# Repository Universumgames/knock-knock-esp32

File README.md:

# Klap-Klap

- [Klap-Klap](#klap-klap)
  - [Description](#description)
  - [Important files and directories](#important-files-and-directories)
  - [Contributing Setup](#contributing-setup)
  - [Project setup](#project-setup)

URL to repository: https://github.com/Universumgames/knock-knock-esp32

## Description
This project is a simple knock pattern recognizer for a door or chest. The knock pattern is stored on an SD card connected to the ESP32. The knock pattern is recognized by the ESP32 and if the pattern is correct, the door or chest is unlocked. The lock is controlled by a solenoid lock. The project is written in C with the ESP-IDF and uses the PlatformIO IDE. The project is based on the ESP32-C3 microcontroller.

## Important files and directories
- [`documentation/sprint_plan.md`](documentation/sprint_plan.md): Contains the Sprint Plan and detailed description by whom the task was completed
- [`documentation/backlog.md`](documentation/backlog.md): Contains the backlog, a detailed beakdown of the seperate task of this project
- [`src/`](src/): Contains the source code of the project
- [`test/`](test/): Contains the test code of the project
- [`platformio.ini`](platformio.ini): Contains the configuration of the project
- [`README.md`](README.md): Contains the description of the project
- [`LICENSE`](LICENSE): Contains the license of the project
- [`CHANGELOG.md`](CHANGELOG.md): The changelog 
- [`lib/`](lib/): Contains the self written libraries
- [`documentation/`](documentation/): Contains the documentation of the project
- [`datasheets/`](datasheets/): Contains the datasheets for the used components
- [`docker/`](docker/): Contains the docker files to build the platformio environment in a docker container
- [`pinout.txt`](pinout.txt): Contains the pinout of the used microcontroller
- [`pcb/`](pcb/): Contains the pcb files

## Contributing Setup
- install clang-format
  - Debian/Ubuntu: `sudo apt install clang-format`
  - Arch: `sudo pacman -S clang`
  - MacOS: `brew install clang-format`
  - Windows: `pip3 install clang-format`
- configure githooks
  - run `git config core.hooksPath .githooks`
- configure IDE to use clang-format
  - VS Code: install the `Clang-Format` extension (https://marketplace.visualstudio.com/items?itemName=xaver.clang-format)
  - CLion: enable clang-format (https://www.jetbrains.com/help/clion/clangformat-as-alternative-formatter.html)

## Project setup

1. Install VS Code
2. Install PlatformIO extension
3. open PIO Home -> Platforms -> Espressif 32 -> Install (should be installed automatically when opening the project via PlatformIO)
4. building the project by clicking on checkmark in the bottom left corner (when hovering over it, it says: "Build")
5. run tests via the `pio test` command in the terminal

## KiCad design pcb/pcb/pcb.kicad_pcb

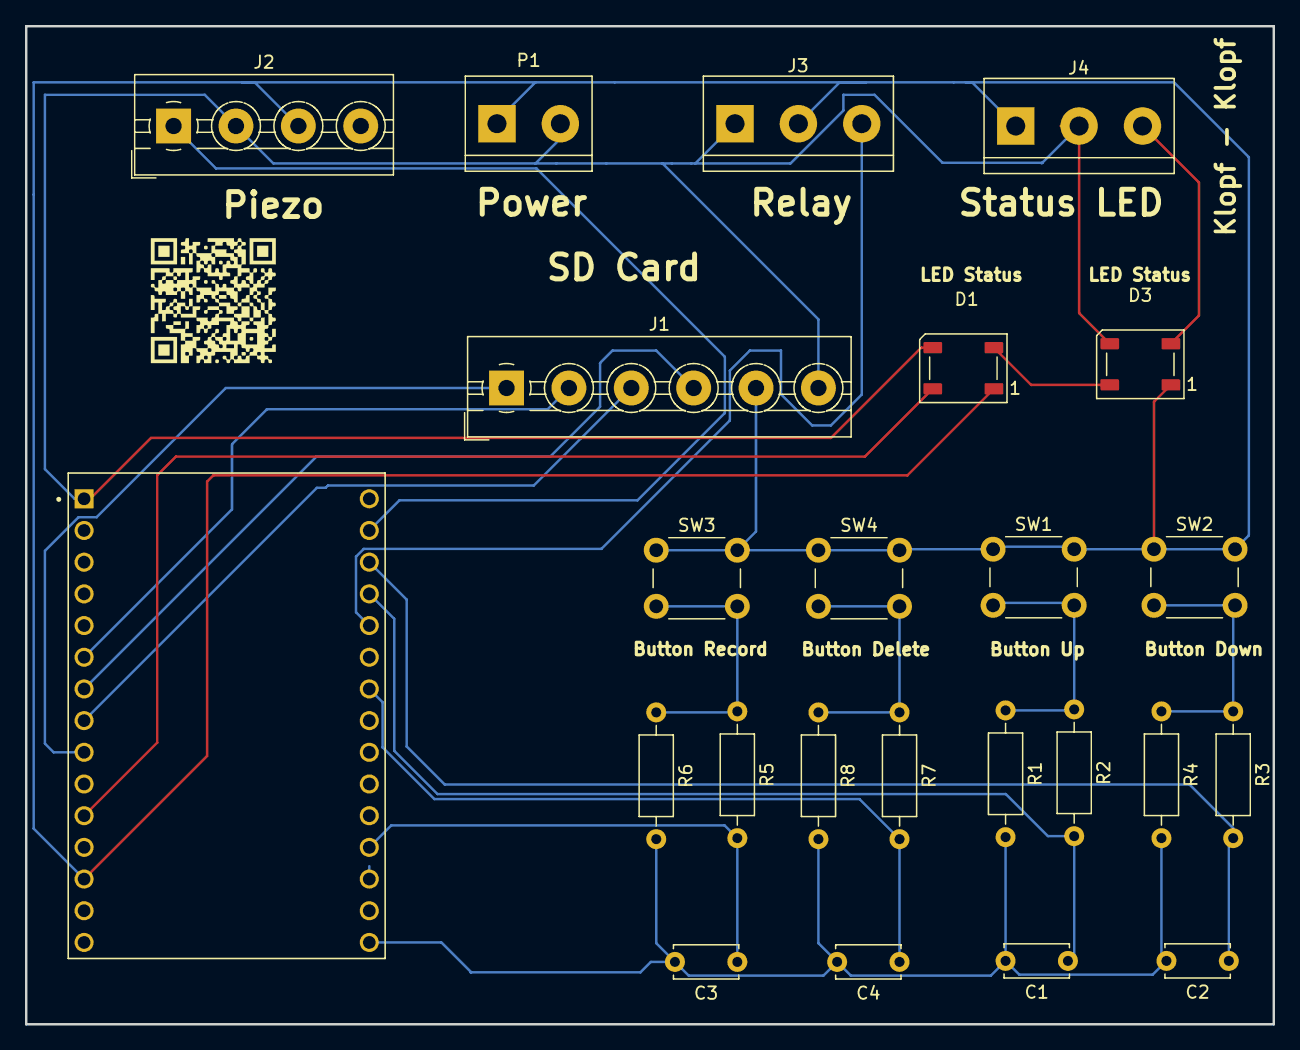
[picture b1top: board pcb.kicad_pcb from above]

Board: 2 copper layers, 100.0 x 80.0 mm, 24 parts (0 on the bottom side), 20 nets.

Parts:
C1, C2, C3, C4: 47nF; C_Disc_D5.0mm_W2.5mm_P5.00mm
D1, D3: WS2812B; LED_WS2812B_PLCC4_5.0x5.0mm_P3.2mm
J1: SD Card; TerminalBlock_MaiXu_MX126-5.0-06P_1x06_P5.00mm
J2: Mic; TerminalBlock_MaiXu_MX126-5.0-04P_1x04_P5.00mm
J3: Relay Solenoid; TerminalBlock_bornier-3_P5.08mm
J4: Status LED; TerminalBlock_bornier-3_P5.08mm
P1: Power; TerminalBlock_bornier-2_P5.08mm
R1, R4, R6, R8: 1kΩ; R_Axial_DIN0207_L6.3mm_D2.5mm_P10.16mm_Horizontal
R2, R3, R5, R7: 10kΩ; R_Axial_DIN0207_L6.3mm_D2.5mm_P10.16mm_Horizontal
SW1: Button Up; SW_PUSH_6mm_H4.3mm
SW2: Button Down; SW_PUSH_6mm_H4.3mm
SW3: Button Record; SW_PUSH_6mm_H4.3mm
SW4: Button Delete; SW_PUSH_6mm_H4.3mm
U1: ESP32-C3-DevKitC-02; XCVR_ESP32-C3-DEVKITC-02

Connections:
3V3: U1.2 (3V3), U1.3 (3V3)
5V: D1.1 (VDD), D3.1 (VDD), J1.5 (5V), J2.3 (5V), J3.2 (5V), J4.1 (5V), P1.1 (5V), SW1.1, SW2.1, SW3.1, SW4.1, U1.13 (5V), U1.14 (5V)
GND: C1.2, C2.2, C3.2, C4.2, D1.3 (VSS), D3.3 (VSS), J1.6 (GND), J2.2 (GND), J3.1 (GND), J4.2 (GND), P1.2 (GND), R1.2, R4.2, R6.2, R8.2, U1.1 (GND), U1.5 (GND), U1.10 (GND), U1.15 (GND), U1.16 (GND), U1.17 (GND), U1.20 (GND), U1.23 (GND), U1.25 (GND), U1.30 (GND)
unnamed: D1.4 (DIN), U1.11 (GPIO8/RGB_LED)
unnamed: D1.2 (DOUT), D3.4 (DIN)
unnamed: D3.2 (DOUT), J4.3 (Data)
unnamed: J1.1 (CS), U1.9 (GPIO7)
unnamed: J1.4 (MISO), U1.7 (GPIO5)
unnamed: J1.3 (MOSI), U1.8 (GPIO6)
unnamed: J1.2 (SCK), U1.6 (GPIO4)
unnamed: J2.1 (A0), U1.29 (GPIO0)
unnamed: J3.3 (S), U1.26 (GPIO3)
unnamed: R1.1, R2.1, SW1.2
unnamed: R3.1, R4.1, SW2.2
unnamed: R5.1, R6.1, SW3.2
unnamed: R7.1, R8.1, SW4.2
unnamed: C2.1, R3.2, U1.28 (GPIO1)
unnamed: C1.1, R2.2, U1.27 (GPIO2)
unnamed: C4.1, R7.2, U1.24 (GPIO10)
unnamed: C3.1, R5.2, U1.19 (GPIO18/USBD_-)

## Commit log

2024-10-04 init
2024-10-04 Add LICENSE
2024-10-04 switch to platformio
2024-10-05 first serial test
2024-10-06 update Serial, switch to cpp
2024-10-06 test assembler
2024-10-06 add cpp formatting config
2024-10-06 play around with hardware led
2024-10-07 bugfixes
2024-10-07 add datasheets
2024-10-07 update backlog
2024-10-08 fix led strip
2024-10-08 refactoring
2024-10-10 finish sprint plan
2024-10-10 test
2024-10-10 init storage
2024-10-10 cleanup main
2024-10-10 fertig heute
2024-10-10 cleanup
2024-10-11 update sprint plant
2024-10-11 add c++ defines
2024-10-11 add documentation to old functions
2024-10-11 implement storage driver first part
2024-10-11 add linked list
2024-10-11 update gitignore
2024-10-13 lock_open fertig
2024-10-13 fixed implementation in linked list
2024-10-13 add new pinout diagram, fix dependencies
2024-10-13 finish basic storage driver
2024-10-14 add pinout list
2024-10-14 finish (revision Tom, Jovan)
2024-10-14 remove all vs code files
2024-10-14 fix library includes
2024-10-14 add pcb
2024-10-14 update pcd mit Notöffnung
2024-10-16 update assets and schematic
2024-10-16 add first documentation file
2024-10-16 preparing documentation
2024-10-16 FInish documentation for Sprint 1 with Simon and Jovan
2024-10-17 update built type
2024-10-17 test ci/cd
2024-10-17 try fixing ci/cd
2024-10-17 try fix 2
2024-10-17 update-README-und-Text-Präsentation
2024-10-17 update Sprintplan
2024-10-17 try ci cd 3
2024-10-17 try cicd fix 4
2024-10-17 cicd try fix 5
2024-10-17 fix cicd try 7
2024-10-18 add testing framework and fix string methods
2024-10-18 fixed unit tests
2024-10-20 add basic definitions
2024-10-20 add fileExists and add comments for common file operations
2024-10-20 add error handling to mounting
2024-10-20 fix bug in lsDir
2024-10-20 add storage test
2024-10-20 add test templates
2024-10-20 fix main
2024-10-21 prepare analog read
2024-10-21 add changelog
2024-10-21 add additional expect for storage test
2024-10-21 preparing further implementation, adding analog read test task
2024-10-22 try fixing led
2024-10-22 implement basic analog read
2024-10-22 try fixing LED driver with spi control, not usable because overwriting storage bus
2024-10-22 add led spi explanation image
2024-10-23 trying out i2s (not working at all)
2024-10-24 trying out i2s lib (not working)
2024-10-24 simplifying rmt config
2024-10-24 simplify and remove old code
2024-10-24 updating basic def header
2024-10-24 update changelog generator
2024-10-24 update cpp header pragma
2024-10-24 add pattern storage
2024-10-25 init pattern storage
2024-10-25 add first code of conduct and contributing
2024-10-25 fix basicdefs
2024-10-25 fix include
2024-10-25 update changelog
2024-10-25 finish pattern storage
2024-10-26 implement pattern storage
2024-10-26 restructure pattern struct to add struct versioning
2024-10-26 adding platform specific definitions and compilations
2024-10-27 fix pattern storage driver and write tests
2024-10-27 add pattern storage test
2024-10-27 implement max function as assembler, add support for platform specific assembler
2024-10-27 in assembly differentiate between arm and x64
2024-10-27 fix esp build
2024-10-27 fix comments in assembly
2024-10-28 fix platform specific assembler
2024-10-28 fix multiplatform build
2024-10-28 retest native assembly
2024-10-28 add knock recordings
2024-10-29 not using x64 assembly
2024-10-29 adding rsicv toolchain installation
2024-10-29 speed up cicd
2024-10-29 fix speedup of cicd
2024-10-29 test cicd
2024-10-29 cicd test
2024-10-29 retest
2024-10-29 adjust cicd to use cache
2024-10-29 from yaml
2024-10-29 try fixing cicd
2024-10-29 fix cicd
2024-10-29 another fix
2024-10-29 moving files, starting to implement pattern recorder
2024-10-29 fix compile
2024-10-30 test cache with symlinks
2024-10-30 fix path
2024-10-30 another ci cache test
2024-10-30 another ci test
2024-10-30 should work now
2024-10-30 use updated gitlab ci file
2024-10-30 fix ci stage test
2024-10-30 Resolve "Muster einspeichern"
2024-10-30 update comments, add code check to cicd
2024-10-30 fix int types
2024-11-01 lib extern led first attempt
2024-11-01 fertig
2024-11-01 pipeline fail korrektur
2024-11-01 add formatter and githooks
2024-11-01 fix platformio.ini corrupted on merge
2024-11-02 update, Anpassungen der Hinweise
2024-11-03 fix analog read
2024-11-03 update clang config
2024-11-03 add automatic file formatting on commit
2024-11-03 retest formatting
2024-11-03 fix formatting in files
2024-11-04 update pcb
2024-11-04 start implementing encoder
2024-11-04 Final_PCB
2024-11-06 test code to get best encoding
2024-11-06 fix removed function
2024-11-06 use pattern encoder
2024-11-07 clang tidy warnings fix, add ring buffer
2024-11-07 use ringbuffer, clang-tidy fixes
2024-11-07 missing pio update
2024-11-07 update pio file
2024-11-07 fix 4mb flash
2024-11-07 missing partition table
2024-11-07 fix string test
2024-11-07 ring buffer fixes and added tests
2024-11-07 add thread prio header
2024-11-07 continue with pattern encoder
2024-11-07 increase maximum opened files
2024-11-07 encoder tests
2024-11-07 add gitignore for old encoder tests
2024-11-07 fix unit tests
2024-11-08 bugfixes and preparing sprint retro
2024-11-11 PCB update
2024-11-11 verkabelung fertig
2024-11-11 finish retro sprint 2
2024-11-11 PCB-Update
2024-11-13 Finale_PCB???
2024-11-13 NochmalFinal
2024-11-15 use global pin definition
2024-11-15 add min function
2024-11-15 update pattern encoder
2024-11-17 fix esp assembly
2024-11-17 fix loging issue
2024-11-17 re-add file storing
2024-11-17 add assembly comments
2024-11-18 Finish 100x80
2024-11-18 FertigEndgültig100x80mm
2024-11-18 Finish
2024-11-18 Finally
2024-11-20 refactoring,
2024-11-20 fix clang tidy
2024-11-20 fix warnings
2024-11-20 refactor to use cached linked lists for pattern storage
2024-11-20 some bugfixes
2024-11-22 fix types, fix one memory bug, update "nextID" generation, improve memory management, fix warnings
2024-11-24 refactoring, adding delta time warnings
2024-11-25 start pattern_play
2024-11-25 implement first draft of pattern matching
2024-11-25 update nochmal weitermachen
2024-11-25 fix multi instance ci/cd
2024-11-25 adding unit tests for matching, bugfixes
2024-11-26 ready?
2024-11-27 add more test cases
2024-11-27 add unit tests for play
2024-11-27 bugfixes in llinked list
2024-11-27 adding second pattern to matcher test
2024-11-27 adding status check to recoder to match and store pattern
2024-11-27 fix compile bugs
2024-11-27 fix warnings in pragma
2024-11-27 create first rough outline for pattern management
2024-12-04 fix assembler conventions
2024-12-04 fix formatting
2024-12-04 add new gitignore entries
2024-12-05 write retro, adjust sprint plan for next sprint
2024-12-05 update linked list to add prev
2024-12-05 PatternManagmentdraft
2024-12-06 fix log
2024-12-06 add numbertoString pragma
2024-12-06 refactoring, trying to add test
2024-12-06 missed file
2024-12-06 wrong tests moved
2024-12-12 add testate templates
2024-12-12 add testate template
2024-12-13 finished testat
2024-12-13 Simon und Jovan
2024-12-19 add first draft of commands
2024-12-19 fix flag header include
2024-12-20 rewrite to allow commands with arguments, string helper functions needed fixing
2024-12-20 missed adding help entry for unlock
2024-12-20 fix unit test
2024-12-29 disable all debug flags by default
2025-01-10 bugfixes, adding new commands
2025-01-12 bomb lab files
2025-01-13 add remove element method
2025-01-13 update pins definition
2025-01-13 fix deletion
2025-01-13 update PatternManagement to autoplay
2025-01-13 update command line
2025-01-13 fix recording
2025-01-13 update gitignore for kicad
2025-01-13 update brightness
2025-01-13 bugfixes for pattern deletion
2025-01-13 update trigger timeout
2025-01-13 update lock OPENTIME
2025-01-13 Schaltplanm
2025-01-13 Change PCB/TEST
2025-01-14 Finale Change PCB
2025-01-15 Sprint 4 Update
2025-01-17 Final Sprint4
2025-01-17 add version hash
2025-01-17 uncomment management
2025-01-20 update sprint plan and readme
2025-01-24 adding pattern encoder reset debug log
2025-01-25 update 3d prints
2025-01-26 renaming 3d print files
